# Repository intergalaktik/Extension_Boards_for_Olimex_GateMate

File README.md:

# Simple extension boards for Olimex GateMate A1 EVB FPGA Board

```
Extensions should be stackable, so you can use 3 extension at once.
Limit for each extension is set by 500mA resetable fuse on the extension board.
This limit of StepUP is currently 400mA if board is using 3V3 or 5V.
```

### adcIO

#### Simple ADC input

```
MAX40079 are wide band, low-noise, low-input bias
current operational amplifiers that offer rail-to-rail outputs
and single-supply operation from 2.7V to 5.5V. These low-
noise amps draw 2.2mA of quiescent supply current per
amplifier. This family of amplifiers offers ultra-low distortion
(0.0002% THD+N), as well as low input voltage-noise
density (4.2nV/√Hz) and low input current-noise density
(0.5fA/√Hz). The low input bias current of 0.3pA (typ) and
low noise(4.5nV/√Hz), together with the wide bandwidth,
provides excellent performance for transimpedance (TIA)
and imaging applications
```

[Schematic](https://github.com/intergalaktik/Extension_Boards_for_Olimex_GateMate/blob/main/adcIO/adcIO.pdf)

[adcIO Request](https://github.com/chili-chips-ba/openCologne/issues/5)

- [x] Schematic
- [x] PCB
- [x] order PCB
- [ ] assemble PCB
- [ ] design confirmed working

### camIO

#### CSI input/ DSI output

```
Raspberry Pi compatible pinout for CSI or DSI.
4 data lines connected.
Two data lines have P and N LP pin connected.
Clock has P LP pin connected.
There are placeholders for on board termination with 100 ohm resistors.
```

[Schematic](https://github.com/intergalaktik/Extension_Boards_for_Olimex_GateMate/blob/main/camIO/camIO.pdf)

- [x] Schematic
- [x] PCB
- [x] order PCB
- [x] assemble PCB
- [ ] design confirmed working

### dualIO

```
Olimex extension to dual PMOD
We are using LSF0108PWR voltage level translator with 3.3V on PMOD side. 
You can two single or one dual PMOD board that works with 3V3.
```

[Schematic](https://github.com/intergalaktik/Extension_Boards_for_Olimex_GateMate/blob/main/dualTranslation/dualTranslation.pdf)

[dualIO Request](https://github.com/chili-chips-ba/openCologne/issues/44)

- [x] Schematic
- [x] PCB
- [x] order PCB
- [x] assemble PCB
- [x] design confirmed working *

* 3V3 volt is not connected on PMOD side - wire can fix that. Once PINS A8 and B8 are set to 0 - PMOD side does the blinks on all pins
* Checked with 64x64 LED panel and it works
* LEvel shifting for aoutput may not be needed - and for input could be done cheaper - https://www.colognechip.com/docs/ug1003-gatemate1-level-shifting-latest.pdf

### dviIO

```
As on ULX3S we have DVI in/out extension we decided to try if it will work on GateMate
```

[Schematic](https://github.com/intergalaktik/Extension_Boards_for_Olimex_GateMate/blob/main/dvi/dvi.pdf)

[dviIO Request](https://github.com/chili-chips-ba/openCologne/issues/46)

- [x] Schematic
- [x] PCB
- [x] order PCB
- [x] assemble PCB
- [x] design confirmed working *

* DVI output is now working great on NA na bank, but losing sync on NB and EB bank

### ethIO

```
The Realtek RTL8211E-VB-CG/RTL8211E-VL-CG/RTL8211EG-VB-CG are highly integrated Ethernet
transceivers that comply with 10Base-T, 100Base-TX, and 1000Base-T IEEE 802.3 standards. They
provide all the necessary physical layer functions to transmit and receive Ethernet packets over CAT.5 UTP
cable.
The RTL8211E-VB(VL)/RTL8211EG-VB uses state-of-the-art DSP technology and an Analog Front End
(AFE) to enable high-speed data transmission and reception over UTP cable. Functions such as Crossover
Detection & Auto-Correction, polarity correction, adaptive equalization, cross-talk cancellation, echo
cancellation, timing recovery, and error correction are implemented in the
RTL8211E-VB(VL)/RTL8211EG-VB to provide robust transmission and reception capabilities at
10Mbps, 100Mbps, or 1000Mbps.
Data transfer between MAC and PHY is via the Reduced Gigabit Media Independent Interface (RGMII) or
Gigabit Media Independent Interface (GMII) for 1000Base-T, 10Base-T, and 100Base-TX. The
RTL8211E-VB and RTL8211EG-VB support 3.3V or 2.5V signaling for RGMII/GMII. The
RTL8211E-VL supports 1.5/1.8V signaling for RGMII
```

[Schematic](https://github.com/intergalaktik/Extension_Boards_for_Olimex_GateMate/blob/main/ethIO/ethIO.pdf)

[ethIO Request](https://github.com/chili-chips-ba/openCologne/issues/40)

This project schematic is from this repository

https://github.com/rishivg/IO-SDR

Board routing is also partially copied

- [x] Schematic
- [x] PCB
- [x] order PCB
- [x] assemble PCB
- [x] design confirmed working *

* Patrick has done some test with Litex and he can communicate with ethernet CHIP

### eduIO

```
While working with Olimex GateMateA1-EVB, we realized that there was only one push-button at user disposal, whereas our TetriSaraj game needed five. Similarly the number of user LEDs is inadequate for debugging (@TsvetanUsunov, take note).

We believe that many other examples would also benefit from a richer complement of LEDs and buttons, and recommend providing a PMOD with an 8-bit bank of each.

Given that this problem is due to GateMate somewhat lower I/O count compared to FPGAs in the same category (@DadoCCAG, take note), these 16 additional lines should come from a GPIO expander based on 1-Wire protocol, and would therefore consume only one FPGA I/O pin for the gain of 16 (or more) slow user I/Os.

To enable this new PMOD hardware, we shall within this project develop RTL for 1-Wire Controller.

PCA9535 is very popular and also available on LCSC and this is just simple extension where we can test 1-Wire Controller.
```

[Schematic](https://github.com/intergalaktik/Extension_Boards_for_Olimex_GateMate/blob/main/eduIO/eduIO.pdf)

[eduIO Request](https://github.com/chili-chips-ba/openCologne/issues/6)

- [x] Schematic
- [x] PCB
- [x] order PCB
- [x] assemble PCB
- [ ] design confirmed working

### MikroBusIO

```
Community request

Along with Dual Pmod - MikroBus allows lot of different boards to be tested..

https://www.mikroe.com/mikrobus

More about this open standard:

https://download.mikroe.com/documents/standards/mikrobus/mikrobus-standard-specification-v200.pdf
```

[Schematic](https://github.com/intergalaktik/Extension_Boards_for_Olimex_GateMate/blob/main/MikroBusIO/MikroBusIO.pdf)

[MikroBusIO Request](https://github.com/chili-chips-ba/openCologne/issues/48)

- [x] Schematic
- [x] PCB
- [x] order PCB
- [x] assemble PCB
- [ ] design confirmed working

### pwrIO

```
Automation, industrial control and robotics projects need to drive motors and actuators. FPGA outputs typically don't have enough current and voltage capability to drive them directly.

While there are many application-specific ICs custom-tuned for a specific load, we are hereby seeking an array of generic power drivers for educational projects, which:

    students can directly drive from FPGA
    and externally connect into a topology of choice (H-Bridge, D-Class Amp, BLDC and AC motor driver, Servos, etc.).

That's to facilitate labs on this subject. While Digilent has a PMOD along these lines, ours should come with more channels and higher power capability:

    https://digilent.com/reference/pmod/pmodoc1/start
    https://digilent.com/reference/pmod/pmodod1/start
    https://digilent.com/reference/pmod/pmodhb5/start

We have also added placeholder for 2 Encoder input's
```

[Schematic](https://github.com/intergalaktik/Extension_Boards_for_Olimex_GateMate/blob/main/pwrIO/pwrIO.pdf)

[pwrIO Request](https://github.com/chili-chips-ba/openCologne/issues/42)

- [x] Schematic
- [x] PCB
- [x] order PCB
- [x] assemble PCB
- [ ] design confirmed working

### simpleIO

```
We needed a controller board for ChiliChipsBa TetriSaraj.
On this simple design we have used Joypad with one aditional button.
On this board we also have I2S audio, and 8 LEDs for debugging purposes. 
```

[Schematic](https://github.com/intergalaktik/Extension_Boards_for_Olimex_GateMate/blob/main/GamePad_I2S_audio_Buttons/KiCad/GamePad_I2S_audio.pdf)

[simpleIO Request](https://github.com/chili-chips-ba/openCologne/issues/9)

- [x] Schematic
- [x] PCB
- [x] order PCB
- [x] assemble PCB
- [x] design confirmed working

### tmrIO

```
ULX3S RTC feature is very cool and unique. But, since not needed for many use-cases, we believe it is better to offer it as an add-on PMOD card.

As Digilent already has such a card:

    https://digilent.com/reference/pmod/pmodrtcc/start
    ours could also come with a relay that allows turning on/off a 2 Amp / 250V consumer. The availability of a power switch would open the RTC to a whole new set of apps without needing additional PMODs

On this board we have I2C RTC chip and two relays that can handle 250V/3A
```

[Schematic](https://github.com/intergalaktik/Extension_Boards_for_Olimex_GateMate/blob/main/tmrIO/tmrIO.pdf)

[tmrIO Request](https://github.com/chili-chips-ba/openCologne/issues/40)

- [x] Schematic
- [x] PCB
- [x] order PCB
- [x] assemble PCB
- [x] design confirmed working *

* Relays are working I did not test I2C RTC

### usbIO

```
USB2.0 is affordable and ubiquitous, with peripherals ranging from HIDs to webcams, and more. However, FPGAs typically don't have a good way of direct interfacing to USB (with a notable exception of Gowin LittleBee lineup). This proposal is to bridge that gap.

We have not seen a similar PMOD on the market. The reason is that it is hard to transfer 480Mbps over a PMOD. Should we manage to do it, we would directly play into the market segment occupied by SPI Camera modules like these:

    https://www.arducam.com/spi-arduino-camera

Our PMOD could be based on one of the following technologies:

    https://www.gowinsemi.com/en/market/featured_detail/13 -- LittleBee FPGA would make it easier to transport 480Mbps over PMOD
    https://verisilicon.com/en/IPPortfolio/USB2PHY
    https://www.ti.com/lit/ds/symlink/tusb1210.pdf

Granted, there are chips that convert USB to SPI, but they are limited to 12Mbps (aka "Full Speed), thus not suitable for cameras.
```

[Schematic](https://github.com/intergalaktik/Extension_Boards_for_Olimex_GateMate/blob/main/USB/USB.pdf)

[usbIO Request](https://github.com/chili-chips-ba/openCologne/issues/43)

- [x] Schematic
- [x] PCB
- [x] order PCB
- [x] assemble PCB
- [ ] design confirmed working

### Olimex Extension template

```
If you want to design your own board, you can use this template!
```

[templateIO folder](https://github.com/intergalaktik/Extension_Boards_for_Olimex_GateMate/tree/main/extension_template)

[Schematic](https://github.com/intergalaktik/Extension_Boards_for_Olimex_GateMate/blob/main/extension_template/extension_template.pdf)

## Work on this boards is financed by NLnet foundation

This project was funded through the NGI0 Entrust Fund, a fund established by NLnet with financial support from the European Commission's Next Generation Internet programme, under the aegis of DG Communications Networks, Content and Technology under grant agreement No 101069594.

This project is done in partnership with Chili.CHIPS.ba

https://www.chili-chips.xyz/

https://nlnet.nl/project/openCologne/

https://github.com/chili-chips-ba/openCologne

## Check up our blogposts

https://intergalaktik.eu/news

## Contact us

Discord: https://discord.gg/qwMUk6W

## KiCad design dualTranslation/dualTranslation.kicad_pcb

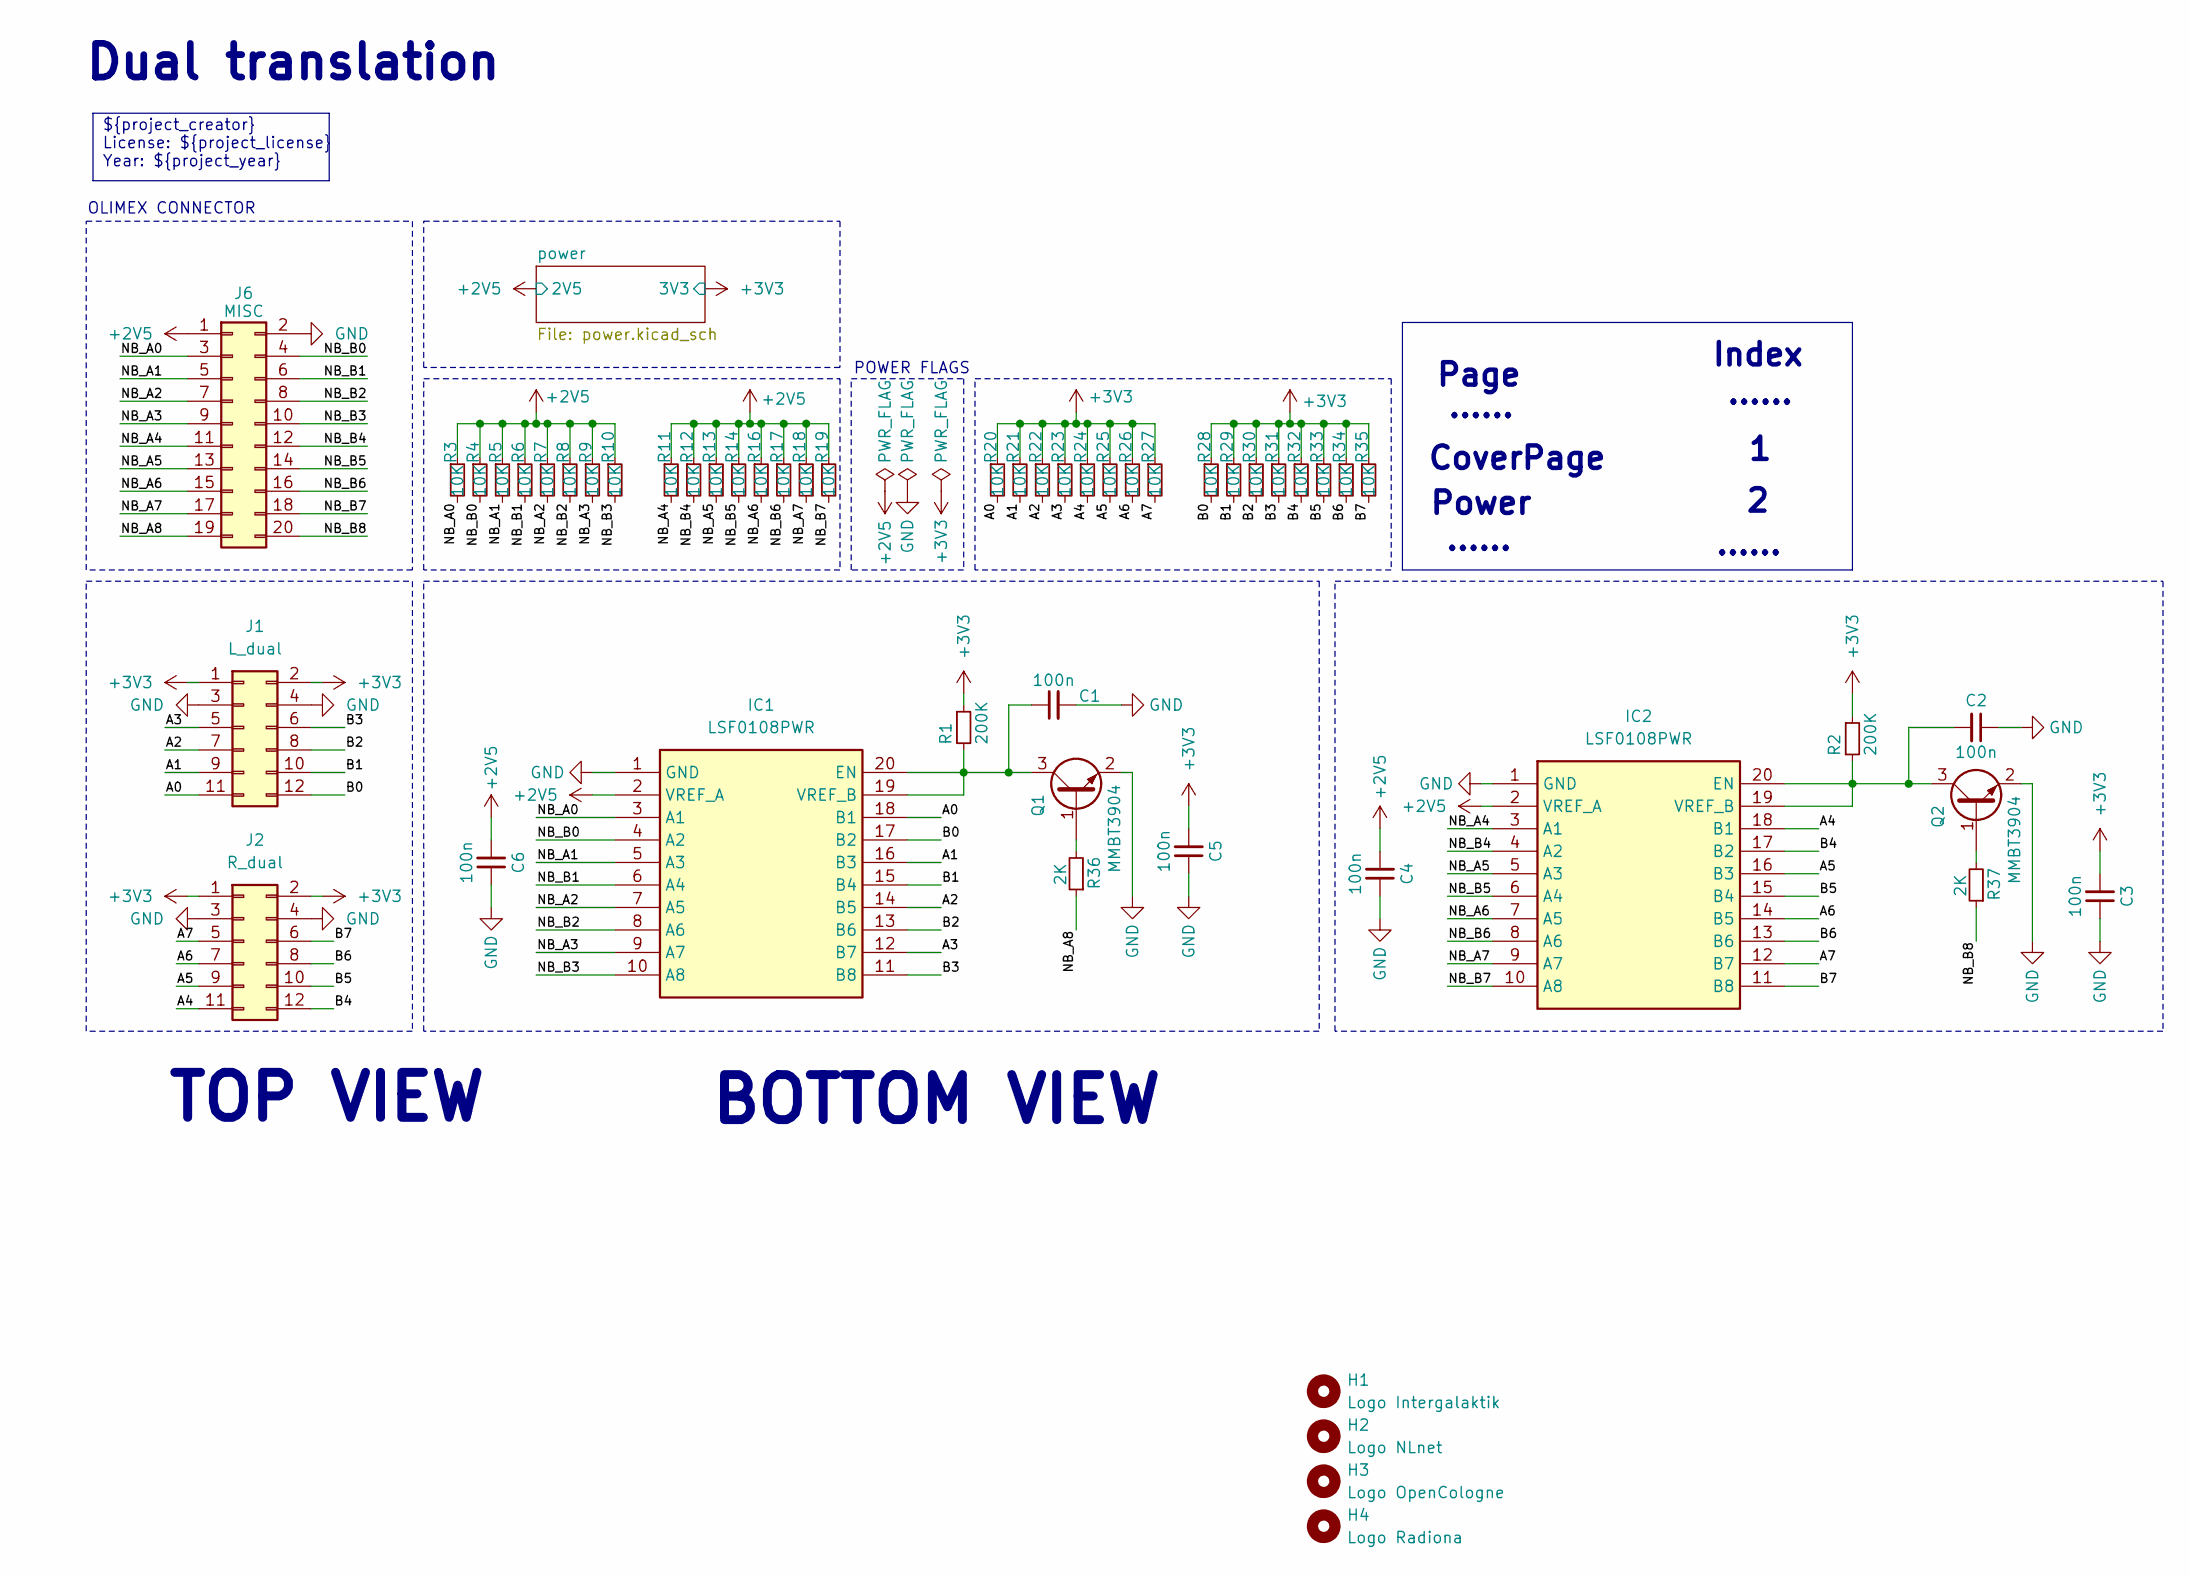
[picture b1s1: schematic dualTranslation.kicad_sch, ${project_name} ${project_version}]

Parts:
C1, C2, C3, C4, C5, C6: 100n; C_0402_1005Metric
H1: Logo Intergalaktik; intergalaktik
H2: Logo NLnet; nlnet
H3: Logo OpenCologne; open_cologne
H4: Logo Radiona; radiona
IC1, IC2: LSF0108PWR; SOP65P640X120-20N; Mouser Part Number 595-LSF0108PWR
J1: L_dual; PinSocket_2x06_P2.54mm_Horizontal
J2: R_dual; PinSocket_2x06_P2.54mm_Horizontal
J6: MISC; PinSocket_2x10_P2.54mm_Vertical_SMD
Q1, Q2: MMBT3904; SOT-23
R1, R2: 200K; R_0402_1005Metric; MPN RC0603FR-071K1L; Mouser 603-RC0603FR-071K1L
R3, R4, R5, R6, R7, R8, R9, R10, R11, R12, R13, R14, R16, R17, R18, R19, R20, R21, R22, R23, R24, R25, R26, R27, R28, R29, R30, R31, R32, R33, R34, R35: 10K; R_0402_1005Metric; MPN RC0603FR-071K1L; Mouser 603-RC0603FR-071K1L
R36, R37: 2K; R_0402_1005Metric; MPN RC0603FR-071K1L; Mouser 603-RC0603FR-071K1L

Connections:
+2V5: C4.2, C6.2, IC1.2 (VREF_A), IC2.2 (VREF_A), J6.1, R3.1, R4.1, R5.1, R6.1, R7.1, R8.1, R9.1, R10.1, R11.1, R12.1, R13.1, R14.1, R16.1, R17.1, R18.1, R19.1; also elsewhere on the board
+3V3: C3.2, C5.2, J1.1, J1.2, J2.1, J2.2, R1.1, R2.1, R20.1, R21.1, R22.1, R23.1, R24.1, R25.1, R26.1, R27.1, R28.1, R29.1, R30.1, R31.1, R32.1, R33.1, R34.1, R35.1; also elsewhere on the board
/A0: IC1.18 (B1), J1.11, R20.2
/A1: IC1.16 (B3), J1.9, R21.2
/A2: IC1.14 (B5), J1.7, R22.2
/A3: IC1.12 (B7), J1.5, R23.2
/A4: IC2.18 (B1), J2.11, R24.2
/A5: IC2.16 (B3), J2.9, R25.2
/A6: IC2.14 (B5), J2.7, R26.2
/A7: IC2.12 (B7), J2.5, R27.2
/B0: IC1.17 (B2), J1.12, R28.2
/B1: IC1.15 (B4), J1.10, R29.2
/B2: IC1.13 (B6), J1.8, R30.2
/B3: IC1.11 (B8), J1.6, R31.2
/B4: IC2.17 (B2), J2.12, R32.2
/B5: IC2.15 (B4), J2.10, R33.2
/B6: IC2.13 (B6), J2.8, R34.2
/B7: IC2.11 (B8), J2.6, R35.2
/NB_A0: IC1.3 (A1), J6.3, R3.2
/NB_A1: IC1.5 (A3), J6.5, R5.2
/NB_A2: IC1.7 (A5), J6.7, R7.2
/NB_A3: IC1.9 (A7), J6.9, R9.2
/NB_A4: IC2.3 (A1), J6.11, R11.2
/NB_A5: IC2.5 (A3), J6.13, R13.2
/NB_A6: IC2.7 (A5), J6.15, R16.2
/NB_A7: IC2.9 (A7), J6.17, R18.2
/NB_A8: J6.19, R36.1
/NB_B0: IC1.4 (A2), J6.4, R4.2
/NB_B1: IC1.6 (A4), J6.6, R6.2
/NB_B2: IC1.8 (A6), J6.8, R8.2
/NB_B3: IC1.10 (A8), J6.10, R10.2
/NB_B4: IC2.4 (A2), J6.12, R12.2
/NB_B5: IC2.6 (A4), J6.14, R14.2
/NB_B6: IC2.8 (A6), J6.16, R17.2
/NB_B7: IC2.10 (A8), J6.18, R19.2
/NB_B8: J6.20, R37.1
GND: C1.2, C2.1, C3.1, C4.1, C5.1, C6.1, IC1.1 (GND), IC2.1 (GND), J1.3, J1.4, J2.3, J2.4, J6.2, Q1.2 (E), Q2.2 (E); also elsewhere on the board
unnamed: C1.1, IC1.19 (VREF_B), IC1.20 (EN), Q1.3 (C), R1.2
unnamed: C2.2, IC2.19 (VREF_B), IC2.20 (EN), Q2.3 (C), R2.2
unnamed: Q1.1 (B), R36.2
unnamed: Q2.1 (B), R37.2

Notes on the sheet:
......
${project_creator} License: ${project_license} Year: ${project_year}
OLIMEX CONNECTOR
Dual translation
CoverPage
Page
Power
Index
TOP VIEW
POWER FLAGS
BOTTOM VIEW

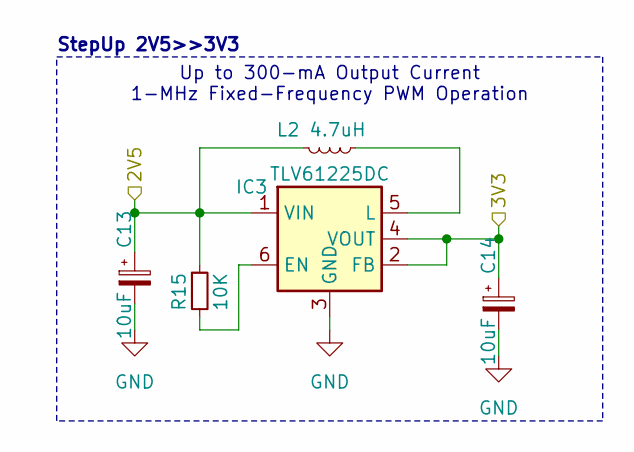
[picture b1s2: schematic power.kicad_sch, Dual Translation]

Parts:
C13, C14: 10uF; C_0402_1005Metric
IC3: TLV61225DC; SOT-363_SC-70-6
L2: 4.7uH; L_0603_1608Metric
R15: 10K; R_0402_1005Metric; MPN RC0603FR-071K1L; Mouser 603-RC0603FR-071K1L

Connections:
+2V5: C13.1, IC3.1 (VIN), L2.2, R15.1; also elsewhere on the board
+3V3: C14.1, IC3.2 (FB), IC3.4 (VOUT); also elsewhere on the board
GND: C13.2, C14.2, IC3.3 (GND); also elsewhere on the board
unnamed: IC3.6 (EN), R15.2
unnamed: IC3.5 (L), L2.1

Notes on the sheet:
Up to 300-mA Output Current 1-MHz Fixed-Frequency PWM Operation
StepUp 2V5>>3V3

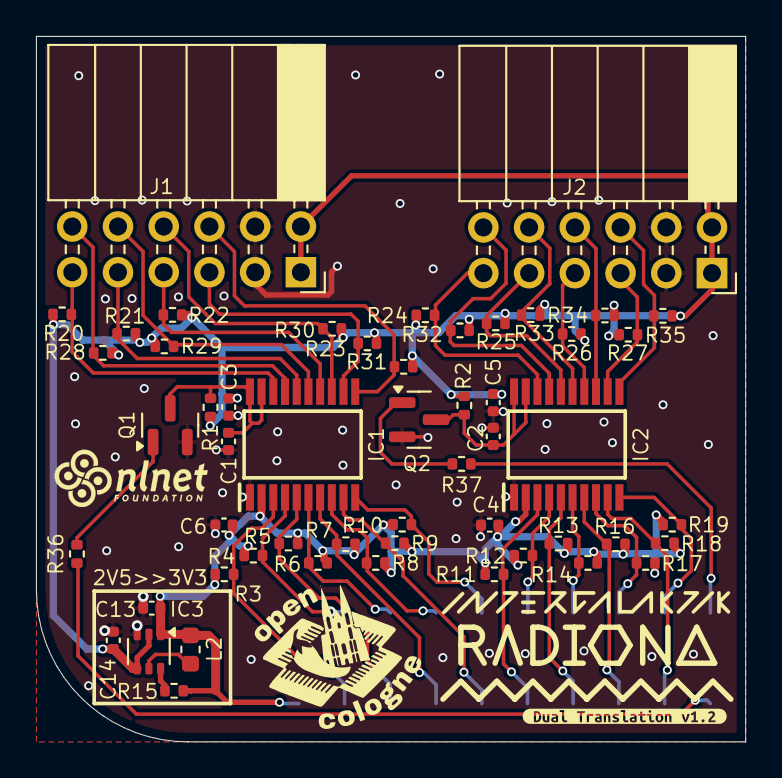
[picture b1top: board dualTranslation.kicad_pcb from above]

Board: 4 copper layers, 39.4 x 39.2 mm, 59 parts (1 on the bottom side), 43 nets.

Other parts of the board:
kibuzzard-686100D9: G***; kibuzzard-686100D9

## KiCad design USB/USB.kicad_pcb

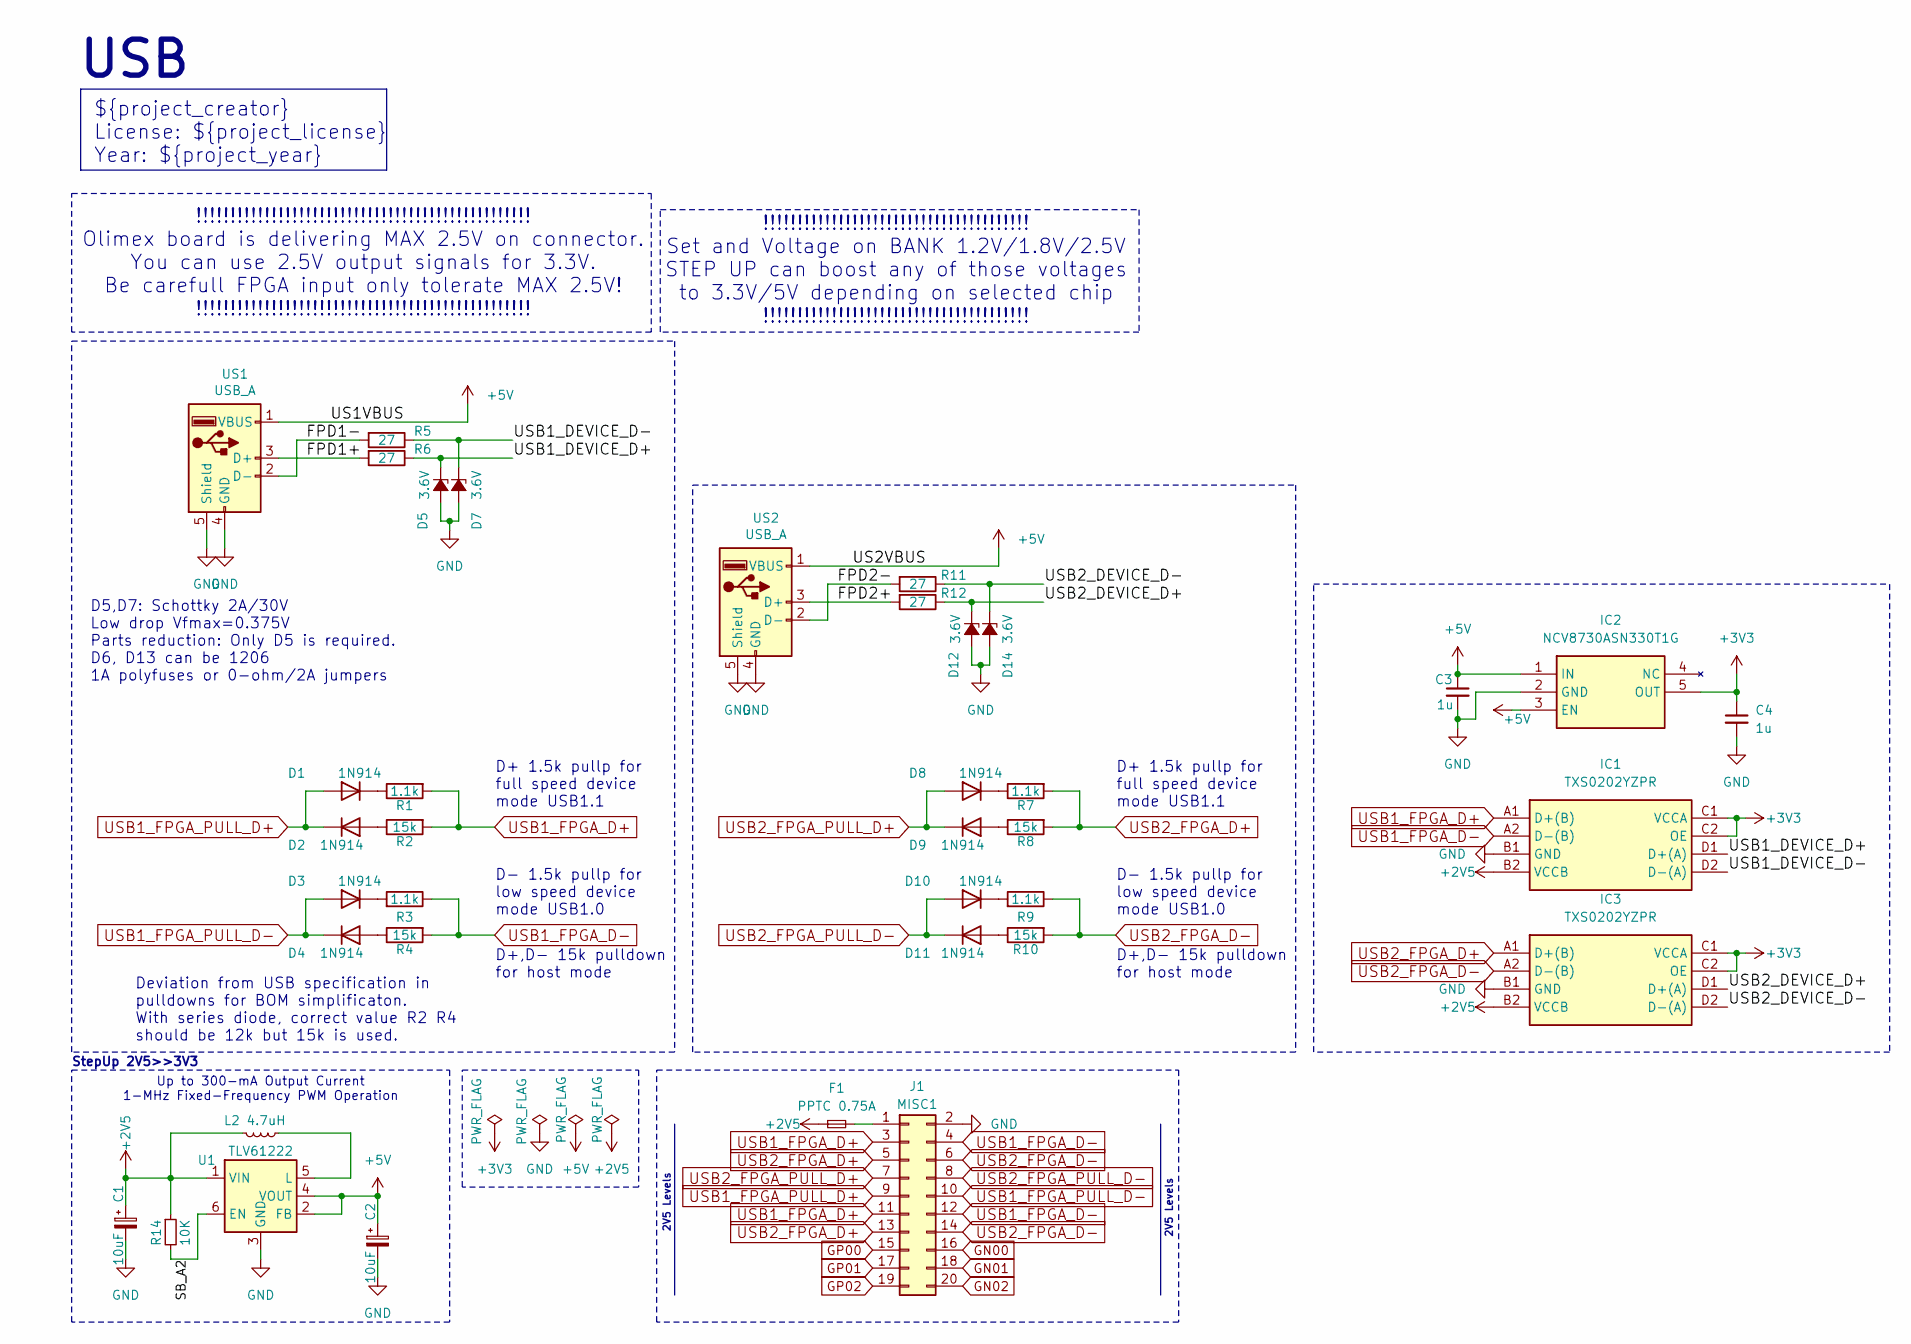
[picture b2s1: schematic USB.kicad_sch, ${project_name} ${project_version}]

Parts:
C1, C2: 10uF; C_0603_1608Metric
C3, C4: 1u; C_0603_1608Metric
D1, D2, D4, D8, D9, D11: 1N914; D_SOD-323_HandSoldering
D3, D10: 1N914; D_SOD-323_HandSoldering; MPN 1N4148WS
D5, D7, D12, D14: 3.6V; D_SOD-323_HandSoldering; MPN BZT52C3V6S; Mouser 833-BZT52C3V6S-TP
F1: PPTC 0.75A; Fuse_1206_3216Metric; Mouser 652-MF-NSMF075-2
IC1, IC3: TXS0202YZPR; BGA8C50P2X4_89X189X50; Mouser Part Number 595-TXS0202YZPR
IC2: NCV8730ASN330T1G; SOT95P275X110-5N; Mouser Part Number 863-NCV8730ASN330T1G
J1: MISC1; PinSocket_2x10_P2.54mm_Vertical_SMD
L2: 4.7uH; L_0603_1608Metric
R1, R3, R7, R9: 1.1k; R_0603_1608Metric
R2, R4, R8, R10: 15k; R_0603_1608Metric
R5, R6, R11, R12: 27; R_0603_1608Metric; MPN AC0603JR-0727RL
R14: 10K; R_0402_1005Metric; MPN RC0603FR-071K1L; Mouser 603-RC0603FR-071K1L
U1: TLV61222; SOT-363_SC-70-6
US1, US2: USB_A; USB_A_Stewart_SS-52100-001_Horizontal

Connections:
+2V5: C1.1, F1.1, IC1.B2 (VCCB), IC3.B2 (VCCB), L2.2, R14.1, U1.1 (VIN)
+3V3: C4.1, IC1.C1 (VCCA), IC1.C2 (OE), IC2.5 (OUT), IC3.C1 (VCCA), IC3.C2 (OE)
+5V: C2.1, C3.1, IC2.1 (IN), IC2.3 (EN), U1.2 (FB), U1.4 (VOUT), US1.1 (VBUS), US2.1 (VBUS)
/FPD1+: R6.2, US1.3 (D+)
/FPD1-: R5.2, US1.2 (D-)
/FPD2+: R12.2, US2.3 (D+)
/FPD2-: R11.2, US2.2 (D-)
/SB_A2: R14.2, U1.6 (EN)
/USB1_DEVICE_D+: D5.1 (K), IC1.D1 (D+(A)), R6.1
/USB1_DEVICE_D-: D7.1 (K), IC1.D2 (D-(A)), R5.1
/USB2_DEVICE_D+: D12.1 (K), IC3.D1 (D+(A)), R12.1
/USB2_DEVICE_D-: D14.1 (K), IC3.D2 (D-(A)), R11.1
GN00: J1.16
GN01: J1.18
GN02: J1.20
GND: C1.2, C2.2, C3.2, C4.2, D5.2 (A), D7.2 (A), D12.2 (A), D14.2 (A), IC1.B1 (GND), IC2.2 (GND), IC3.B1 (GND), J1.2, U1.3 (GND), US1.4 (GND), US1.5 (Shield), US2.4 (GND), US2.5 (Shield)
GP00: J1.15
GP01: J1.17
GP02: J1.19
unnamed: D1.1 (K), R1.1
unnamed: D2.2 (A), R2.1
unnamed: D3.1 (K), R3.2
unnamed: D4.2 (A), R4.1
unnamed: D8.1 (K), R7.1
unnamed: D9.2 (A), R8.1
unnamed: D10.1 (K), R9.2
unnamed: D11.2 (A), R10.1
unnamed: F1.2, J1.1
unnamed: L2.1, U1.5 (L)
USB1_FPGA_D+: IC1.A1 (D+(B)), J1.3, J1.11, R1.2, R2.2
USB1_FPGA_D-: IC1.A2 (D-(B)), J1.4, J1.12, R3.1, R4.2
USB1_FPGA_PULL_D+: D1.2 (A), D2.1 (K), J1.9
USB1_FPGA_PULL_D-: D3.2 (A), D4.1 (K), J1.10
USB2_FPGA_D+: IC3.A1 (D+(B)), J1.5, J1.13, R7.2, R8.2
USB2_FPGA_D-: IC3.A2 (D-(B)), J1.6, J1.14, R9.1, R10.2
USB2_FPGA_PULL_D+: D8.2 (A), D9.1 (K), J1.7
USB2_FPGA_PULL_D-: D10.2 (A), D11.1 (K), J1.8

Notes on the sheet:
2V5 Levels
D+,D- 15k pulldown for host mode
Up to 300-mA Output Current 1-MHz Fixed-Frequency PWM Operation
Deviation from USB specification in pulldowns for BOM simplificaton. With series diode, correct value R2 R4 should be 12k but 15k is used.
D+ 1.5k pullp for full speed device mode USB1.1
!!!!!!!!!!!!!!!!!!!!!!!!!!!!!!!!!!!!!!!!!!!!!!!!! Olimex board is delivering MAX 2.5V on connector. You can use 2.5V output signals for 3.3V. Be carefull FPGA input only tolerate MAX 2.5V! !!!!!!!!!!!!!!!!!!!!!!!!!!!!!!!!!!!!!!!!!!!!!!!!!
D- 1.5k pullp for low speed device mode USB1.0
StepUp 2V5>>3V3
${project_creator} License: ${project_license} Year: ${project_year}
D5,D7: Schottky 2A/30V Low drop Vfmax=0.375V Parts reduction: Only D5 is required. D6, D13 can be 1206 1A polyfuses or 0-ohm/2A jumpers
USB
!!!!!!!!!!!!!!!!!!!!!!!!!!!!!!!!!!!!!!! Set and Voltage on BANK 1.2V/1.8V/2.5V STEP UP can boost any of those voltages to 3.3V/5V depending on selected chip !!!!!!!!!!!!!!!!!!!!!!!!!!!!!!!!!!!!!!!

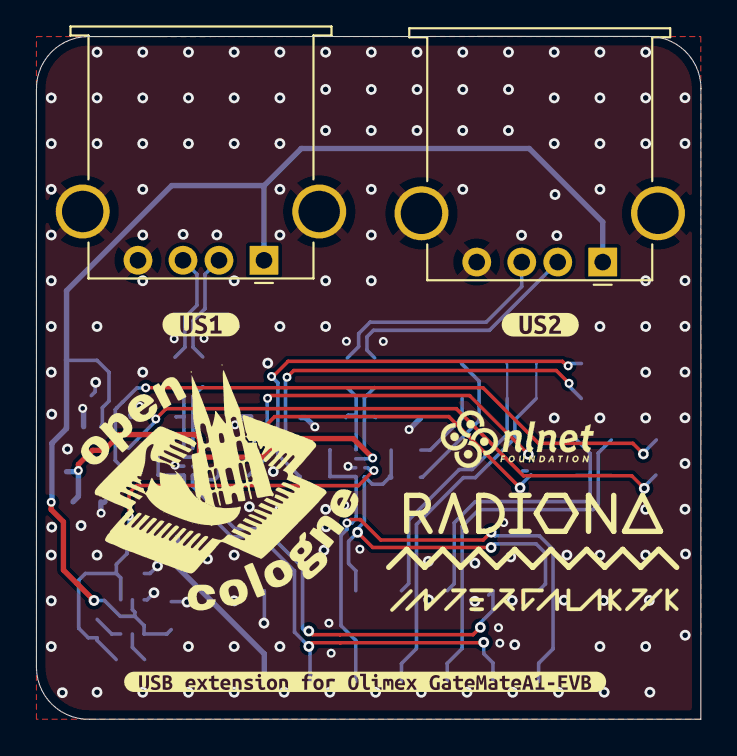
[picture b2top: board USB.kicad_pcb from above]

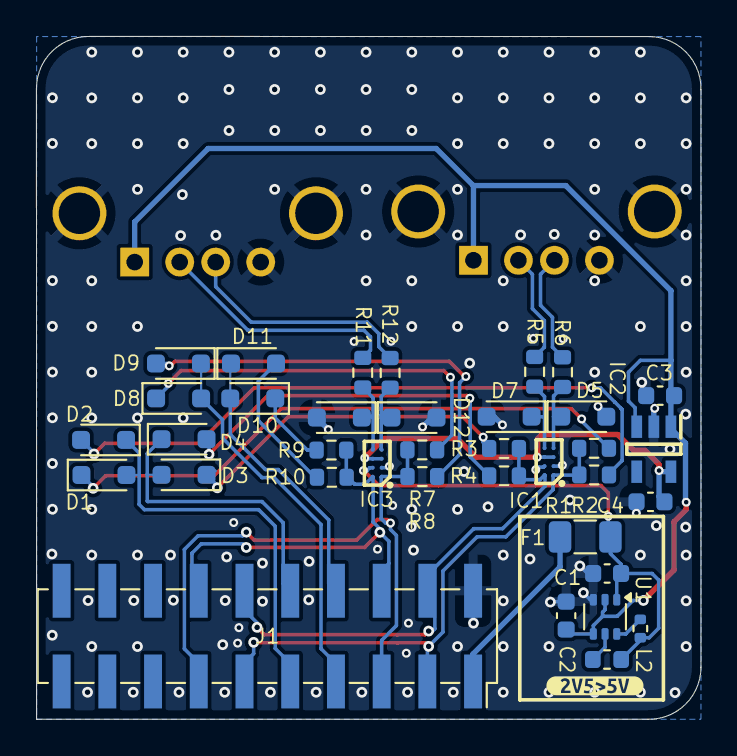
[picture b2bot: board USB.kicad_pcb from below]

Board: 4 copper layers, 36.9 x 37.9 mm, 46 parts (37 on the bottom side), 31 nets.

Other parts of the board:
Intergalaktik: Intergalaktik; Intergalaktik logo
NLNet: NLNet; nlnet
OpenCologne: OpenCologne; open_cologne
kibuzzard-67445C48: G***; kibuzzard-67445C48
kibuzzard-67445D8F: G***; kibuzzard-67445D8F
kibuzzard-674459A0: G***; kibuzzard-674459A0
kibuzzard-6744599A: G***; kibuzzard-6744599A
radiona: radiona

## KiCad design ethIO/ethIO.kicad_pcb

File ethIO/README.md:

## ethIO

This project schematic is from this repository

https://github.com/rishivg/IO-SDR

Board routing is also partially copied

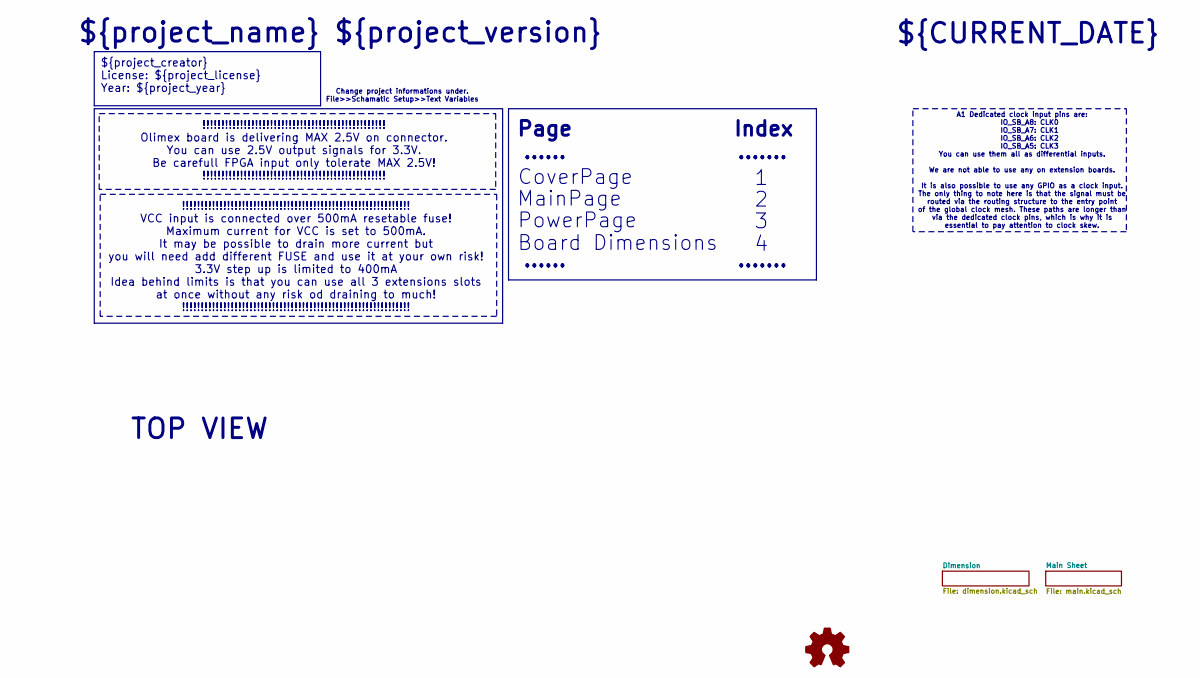
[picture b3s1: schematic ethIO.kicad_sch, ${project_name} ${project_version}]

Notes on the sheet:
${project_creator} License: ${project_license} Year: ${project_year}
Index
!!!!!!!!!!!!!!!!!!!!!!!!!!!!!!!!!!!!!!!!!!!!!!!!!!!!!!!!!!!!! VCC input is connected over 500mA resetable fuse! Maximum current for VCC is set to 500mA. It may be possible to drain more current but you will need add different FUSE and use it at your own risk! 3.3V step up is limited to 400mA Idea b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
!!!!!!!!!!!!!!!!!!!!!!!!!!!!!!!!!!!!!!!!!!!!!!!!! Olimex board is delivering MAX 2.5V on connector. You can use 2.5V output signals for 3.3V. Be carefull FPGA input only tolerate MAX 2.5V! !!!!!!!!!!!!!!!!!!!!!!!!!!!!!!!!!!!!!!!!!!!!!!!!!
......
PowerPage
Change project informations under. File>>Schamatic Setup>>Text Variables
.......
A1 Dedicated clock input pins are: IO_SB_A8: CLK0 IO_SB_A7: CLK1 IO_SB_A6: CLK2 IO_SB_A5: CLK3 You can use them all as differential inputs. We are not able to use any on extension boards. It is also possible to use any GPIO as a clock input. The only thing to note here is that the signal must be ro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
CoverPage
Board Dimensions
MainPage
${CURRENT_DATE}
${project_name} ${project_version}
TOP VIEW
Page

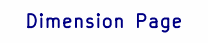
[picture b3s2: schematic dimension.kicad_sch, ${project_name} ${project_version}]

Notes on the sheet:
Dimension Page

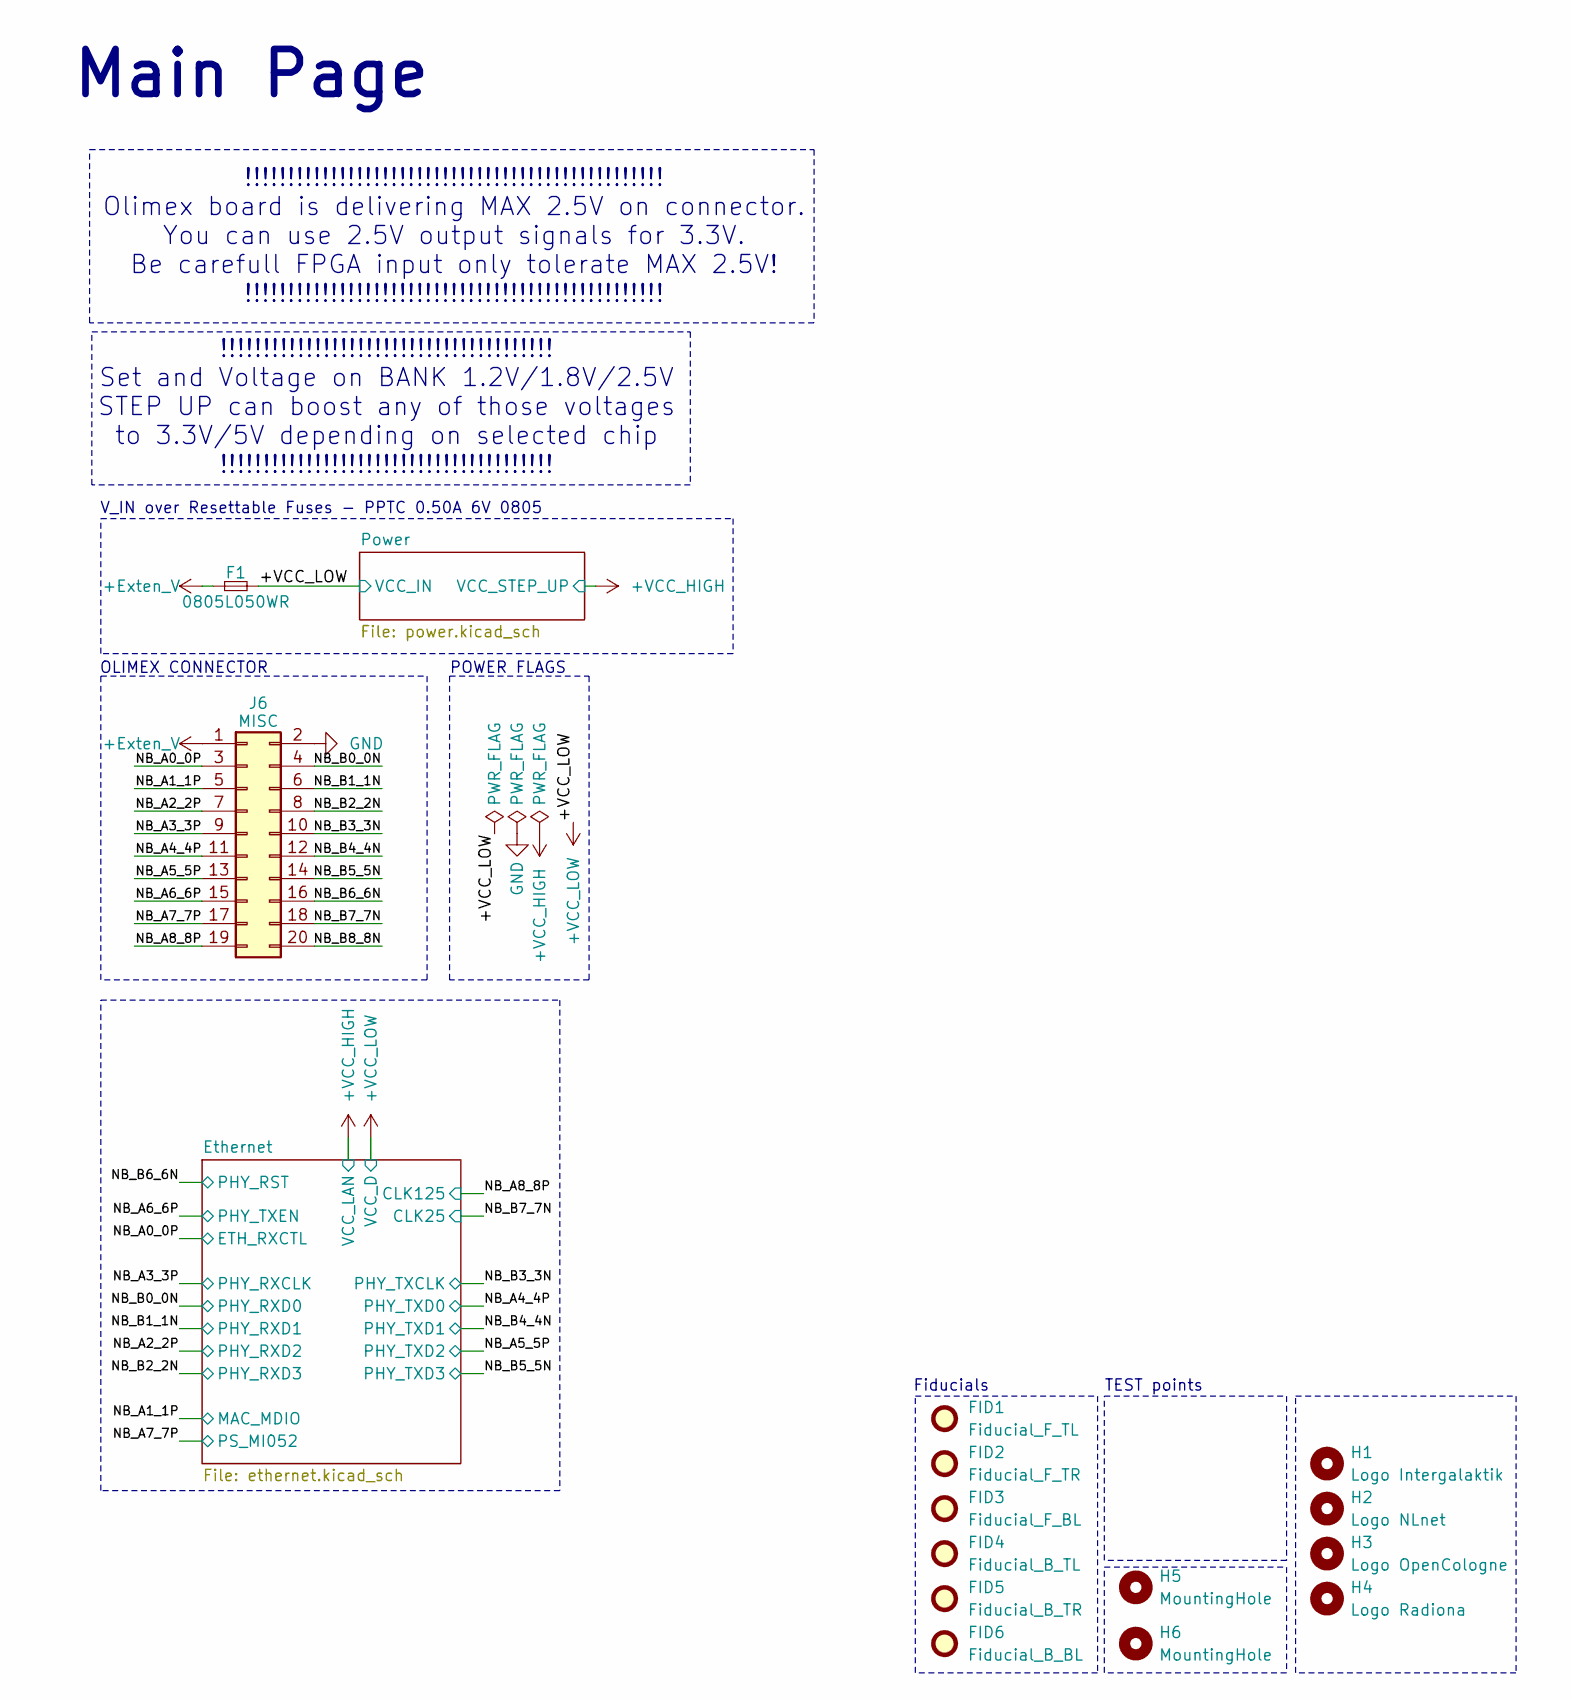
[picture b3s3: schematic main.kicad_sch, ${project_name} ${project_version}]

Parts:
F1: 0805L050WR; Fuse_0805_2012Metric
FID1: Fiducial_F_TL; Fiducial_0.5mm_Mask1mm
FID2: Fiducial_F_TR; Fiducial_0.5mm_Mask1mm
FID3: Fiducial_F_BL; Fiducial_0.5mm_Mask1mm
FID4: Fiducial_B_TL; Fiducial_0.5mm_Mask1mm
FID5: Fiducial_B_TR; Fiducial_0.5mm_Mask1mm
FID6: Fiducial_B_BL; Fiducial_0.5mm_Mask1mm
H1: Logo Intergalaktik; intergalaktik
H2: Logo NLnet; nlnet
H3: Logo OpenCologne; open_cologne_small
H4: Logo Radiona; radiona_small
H5, H6: MountingHole; MountingHole_2.2mm_M2
J6: MISC; PinSocket_2x10_P2.54mm_Vertical_SMD

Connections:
+Exten_V: F1.1, J6.1
+VCC_LOW: F1.2; also elsewhere on the board
/Main Sheet/NB_A0_0P: J6.3; also elsewhere on the board
/Main Sheet/NB_A1_1P: J6.5; also elsewhere on the board
/Main Sheet/NB_A2_2P: J6.7; also elsewhere on the board
/Main Sheet/NB_A3_3P: J6.9; also elsewhere on the board
/Main Sheet/NB_A4_4P: J6.11; also elsewhere on the board
/Main Sheet/NB_A5_5P: J6.13; also elsewhere on the board
/Main Sheet/NB_A6_6P: J6.15; also elsewhere on the board
/Main Sheet/NB_A7_7P: J6.17; also elsewhere on the board
/Main Sheet/NB_A8_8P: J6.19; also elsewhere on the board
/Main Sheet/NB_B0_0N: J6.4; also elsewhere on the board
/Main Sheet/NB_B1_1N: J6.6; also elsewhere on the board
/Main Sheet/NB_B2_2N: J6.8; also elsewhere on the board
/Main Sheet/NB_B3_3N: J6.10; also elsewhere on the board
/Main Sheet/NB_B4_4N: J6.12; also elsewhere on the board
/Main Sheet/NB_B5_5N: J6.14; also elsewhere on the board
/Main Sheet/NB_B6_6N: J6.16; also elsewhere on the board
/Main Sheet/NB_B7_7N: J6.18; also elsewhere on the board
/Main Sheet/NB_B8_8N: J6.20
GND: J6.2; also elsewhere on the board

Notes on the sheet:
TEST points
POWER FLAGS
V_IN over Resettable Fuses - PPTC 0.50A 6V 0805
!!!!!!!!!!!!!!!!!!!!!!!!!!!!!!!!!!!!!!!!!!!!!!!!! Olimex board is delivering MAX 2.5V on connector. You can use 2.5V output signals for 3.3V. Be carefull FPGA input only tolerate MAX 2.5V! !!!!!!!!!!!!!!!!!!!!!!!!!!!!!!!!!!!!!!!!!!!!!!!!!
Fiducials
OLIMEX CONNECTOR
Main Page
!!!!!!!!!!!!!!!!!!!!!!!!!!!!!!!!!!!!!!! Set and Voltage on BANK 1.2V/1.8V/2.5V STEP UP can boost any of those voltages to 3.3V/5V depending on selected chip !!!!!!!!!!!!!!!!!!!!!!!!!!!!!!!!!!!!!!!

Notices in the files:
GamePad_I2S_audio/KiCad/GamePad_I2S_audio.kicad_sch:
CERN-OHL-S v2
parts and their libraries:
project_license: CERN-OHL-S v2
project_license: GPL-3.0
